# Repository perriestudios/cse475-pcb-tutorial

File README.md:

# <p align="center"> [CSE/EE 475] PCB Tutorial </p>

This repository contains all the files used for the PCB tutorial I taught in the Embedded Systems Capstone class. The base design was derived from the work of Mike's(MalphasWats) [**hawk**](https://github.com/MalphasWats/hawk) project. Hawk is well documented and highlights most concepts of PCB Design required for this class.

I made the following changes to the design to ensure a few other useful concepts were also covered:

- Added a different tactile switch to demonstrate the addition of external libraries, pull-ups
- Added a 'Builtin_LED' because it is a useful feature to have
- Moved the 'Tactile Switch and Builtin_LED' circuitry to the bottom layer to demonstrate component placement and routing on two layers
- Added 'GND' copper pour to top layer and '3V3' copper pour on bottom layer to demonstrate the use of copper pours
- Added UW logo on the top silkscreen layer to demonstrate the process of importing graphics into PCB
- Added text in the bottom silksreen layer to demonstrate the addition of useful text
- Generated Gerber files for the changes made above

The schematic with the changes looks like this:

Here's how the completed PCB looks like:

The slides used for the presentation can be found [here](https://docs.google.com/presentation/d/1yJ8d16ENtwlgDVSCv_pk9EhUhwFI2H66Mtzrn_bvfB8/edit?usp=sharing) and the dxf file imported into the design can be found [here](https://drive.google.com/file/d/1Wx1g2NUie0CLL9HZYDxmSbAbv8WsBbdb/view)

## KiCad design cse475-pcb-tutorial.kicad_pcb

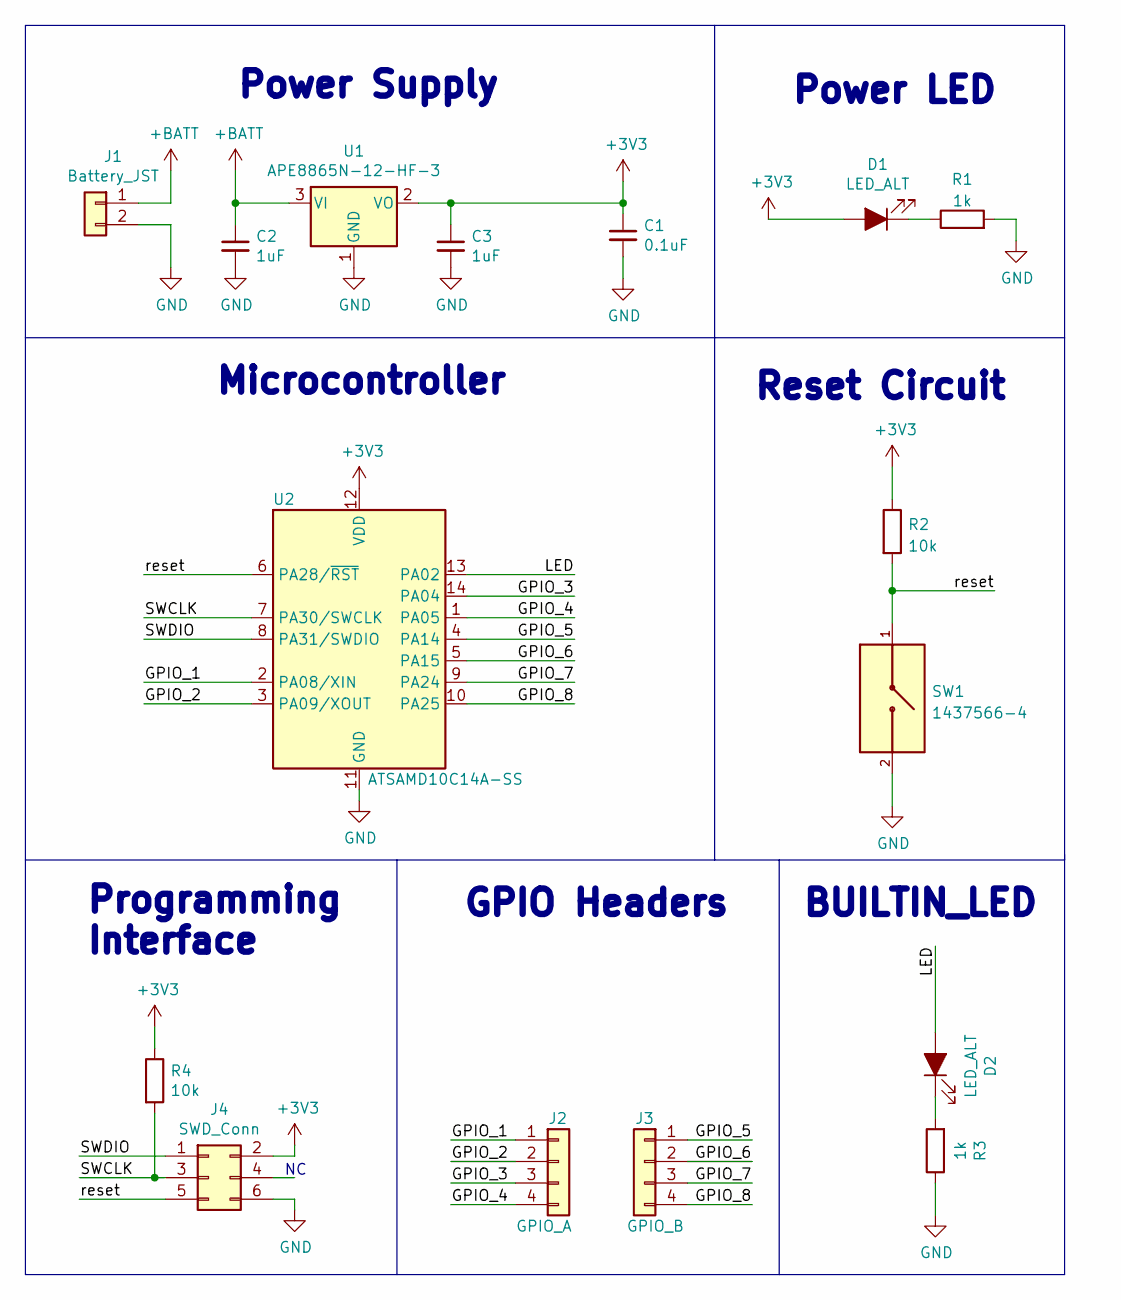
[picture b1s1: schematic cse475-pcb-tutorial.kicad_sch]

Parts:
C1: 0.1uF; C_0805_2012Metric_Pad1.15x1.40mm_HandSolder
C2, C3: 1uF; C_0805_2012Metric_Pad1.15x1.40mm_HandSolder
D1, D2: LED_ALT; LED_0805_2012Metric_Pad1.15x1.40mm_HandSolder
J1: Battery_JST; JST_PH_B2B-PH-K_1x02_P2.00mm_Vertical
J2: GPIO_A; PinHeader_1x04_P2.54mm_Vertical
J3: GPIO_B; PinHeader_1x04_P2.54mm_Vertical
J4: SWD_Conn; PinHeader_2x03_P2.54mm_Vertical
R1: 1k; R_0805_2012Metric_Pad1.20x1.40mm_HandSolder
R2: 10k; R_0805_2012Metric_Pad1.20x1.40mm_HandSolder
R3: 1k; R_0805_2012Metric_Pad1.15x1.40mm_HandSolder
R4: 10k; R_0805_2012Metric_Pad1.15x1.40mm_HandSolder
SW1: 1437566-4; SW_1437566-4
U1: APE8865N-12-HF-3; SOT-23
U2: ATSAMD10C14A-SS; SOIC-14_3.9x8.7mm_P1.27mm

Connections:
+3V3: C1.1, C3.1, D1.2 (A), J4.2, R2.1, R4.1, U1.2 (VO), U2.12 (VDD)
+BATT: C2.1, J1.1, U1.3 (VI)
/GPIO_1: J2.1, U2.2 (PA08/XIN)
/GPIO_2: J2.2, U2.3 (PA09/XOUT)
/GPIO_3: J2.3, U2.14 (PA04)
/GPIO_4: J2.4, U2.1 (PA05)
/GPIO_5: J3.1, U2.4 (PA14)
/GPIO_6: J3.2, U2.5 (PA15)
/GPIO_7: J3.3, U2.9 (PA24)
/GPIO_8: J3.4, U2.10 (PA25)
/LED: D2.2 (A), U2.13 (PA02)
/SWCLK: J4.3, R4.2, U2.7 (PA30/SWCLK)
/SWDIO: J4.1, U2.8 (PA31/SWDIO)
/reset: J4.5, R2.2, SW1.1, U2.6 (PA28/~RST)
GND: C1.2, C2.2, C3.2, J1.2, J4.6, R1.2, R3.1, SW1.2, U1.1 (GND), U2.11 (GND)
unnamed: D1.1 (K), R1.1
unnamed: D2.1 (K), R3.2

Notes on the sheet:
Power LED
BUILTIN_LED
Programming Interface
Reset Circuit
GPIO Headers
Power Supply
Microcontroller

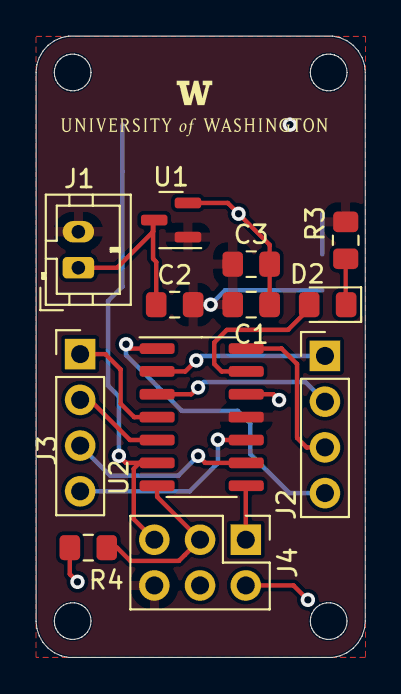
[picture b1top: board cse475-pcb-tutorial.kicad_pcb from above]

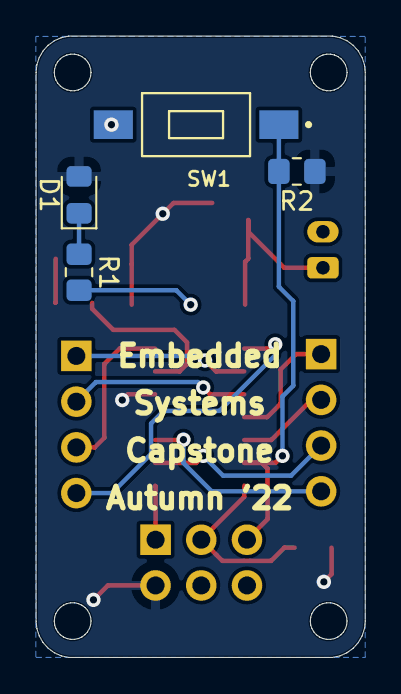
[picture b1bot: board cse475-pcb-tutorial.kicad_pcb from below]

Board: 2 copper layers, 18.3 x 34.5 mm, 16 parts (4 on the bottom side), 17 nets.

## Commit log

2022-10-27 commiting all files
2022-10-27 fixing broken images
2022-10-28 Update README.md
    Corrected typo in readme
